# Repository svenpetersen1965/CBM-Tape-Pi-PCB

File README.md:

# CBM-Tape-Pi-PCB
# Preliminary Release of Rev.2
This is the PCB, that I have created for <a href="https://github.com/RhinoDevel/cbmtapepi">RhinoDevel's CBM Tape Pi</a>.

It is <b>not yet tested</b> and this is only a <b>preliminary</b> release!

The PCB has an option for a barrel connector Power Supply. Also, for possible future software development, a rotary encode and an I²C OLED-Display can be connected. This is not yet supported.

Debugging result so far:

There is a screw up with signals <b>BCM11</b>, it shoudl be connected to the collector of Q4, but the signal name is screwed up. A botch wire is required between the collector of Q4/R8 and Pin 23/BCM11 of the Raspberry Pi.

# Rev. 3
Rev. 3 fixes the bug of rev. 2. Also the dimensions have changed: the RasPi was moved 4mm away from the edge connector.

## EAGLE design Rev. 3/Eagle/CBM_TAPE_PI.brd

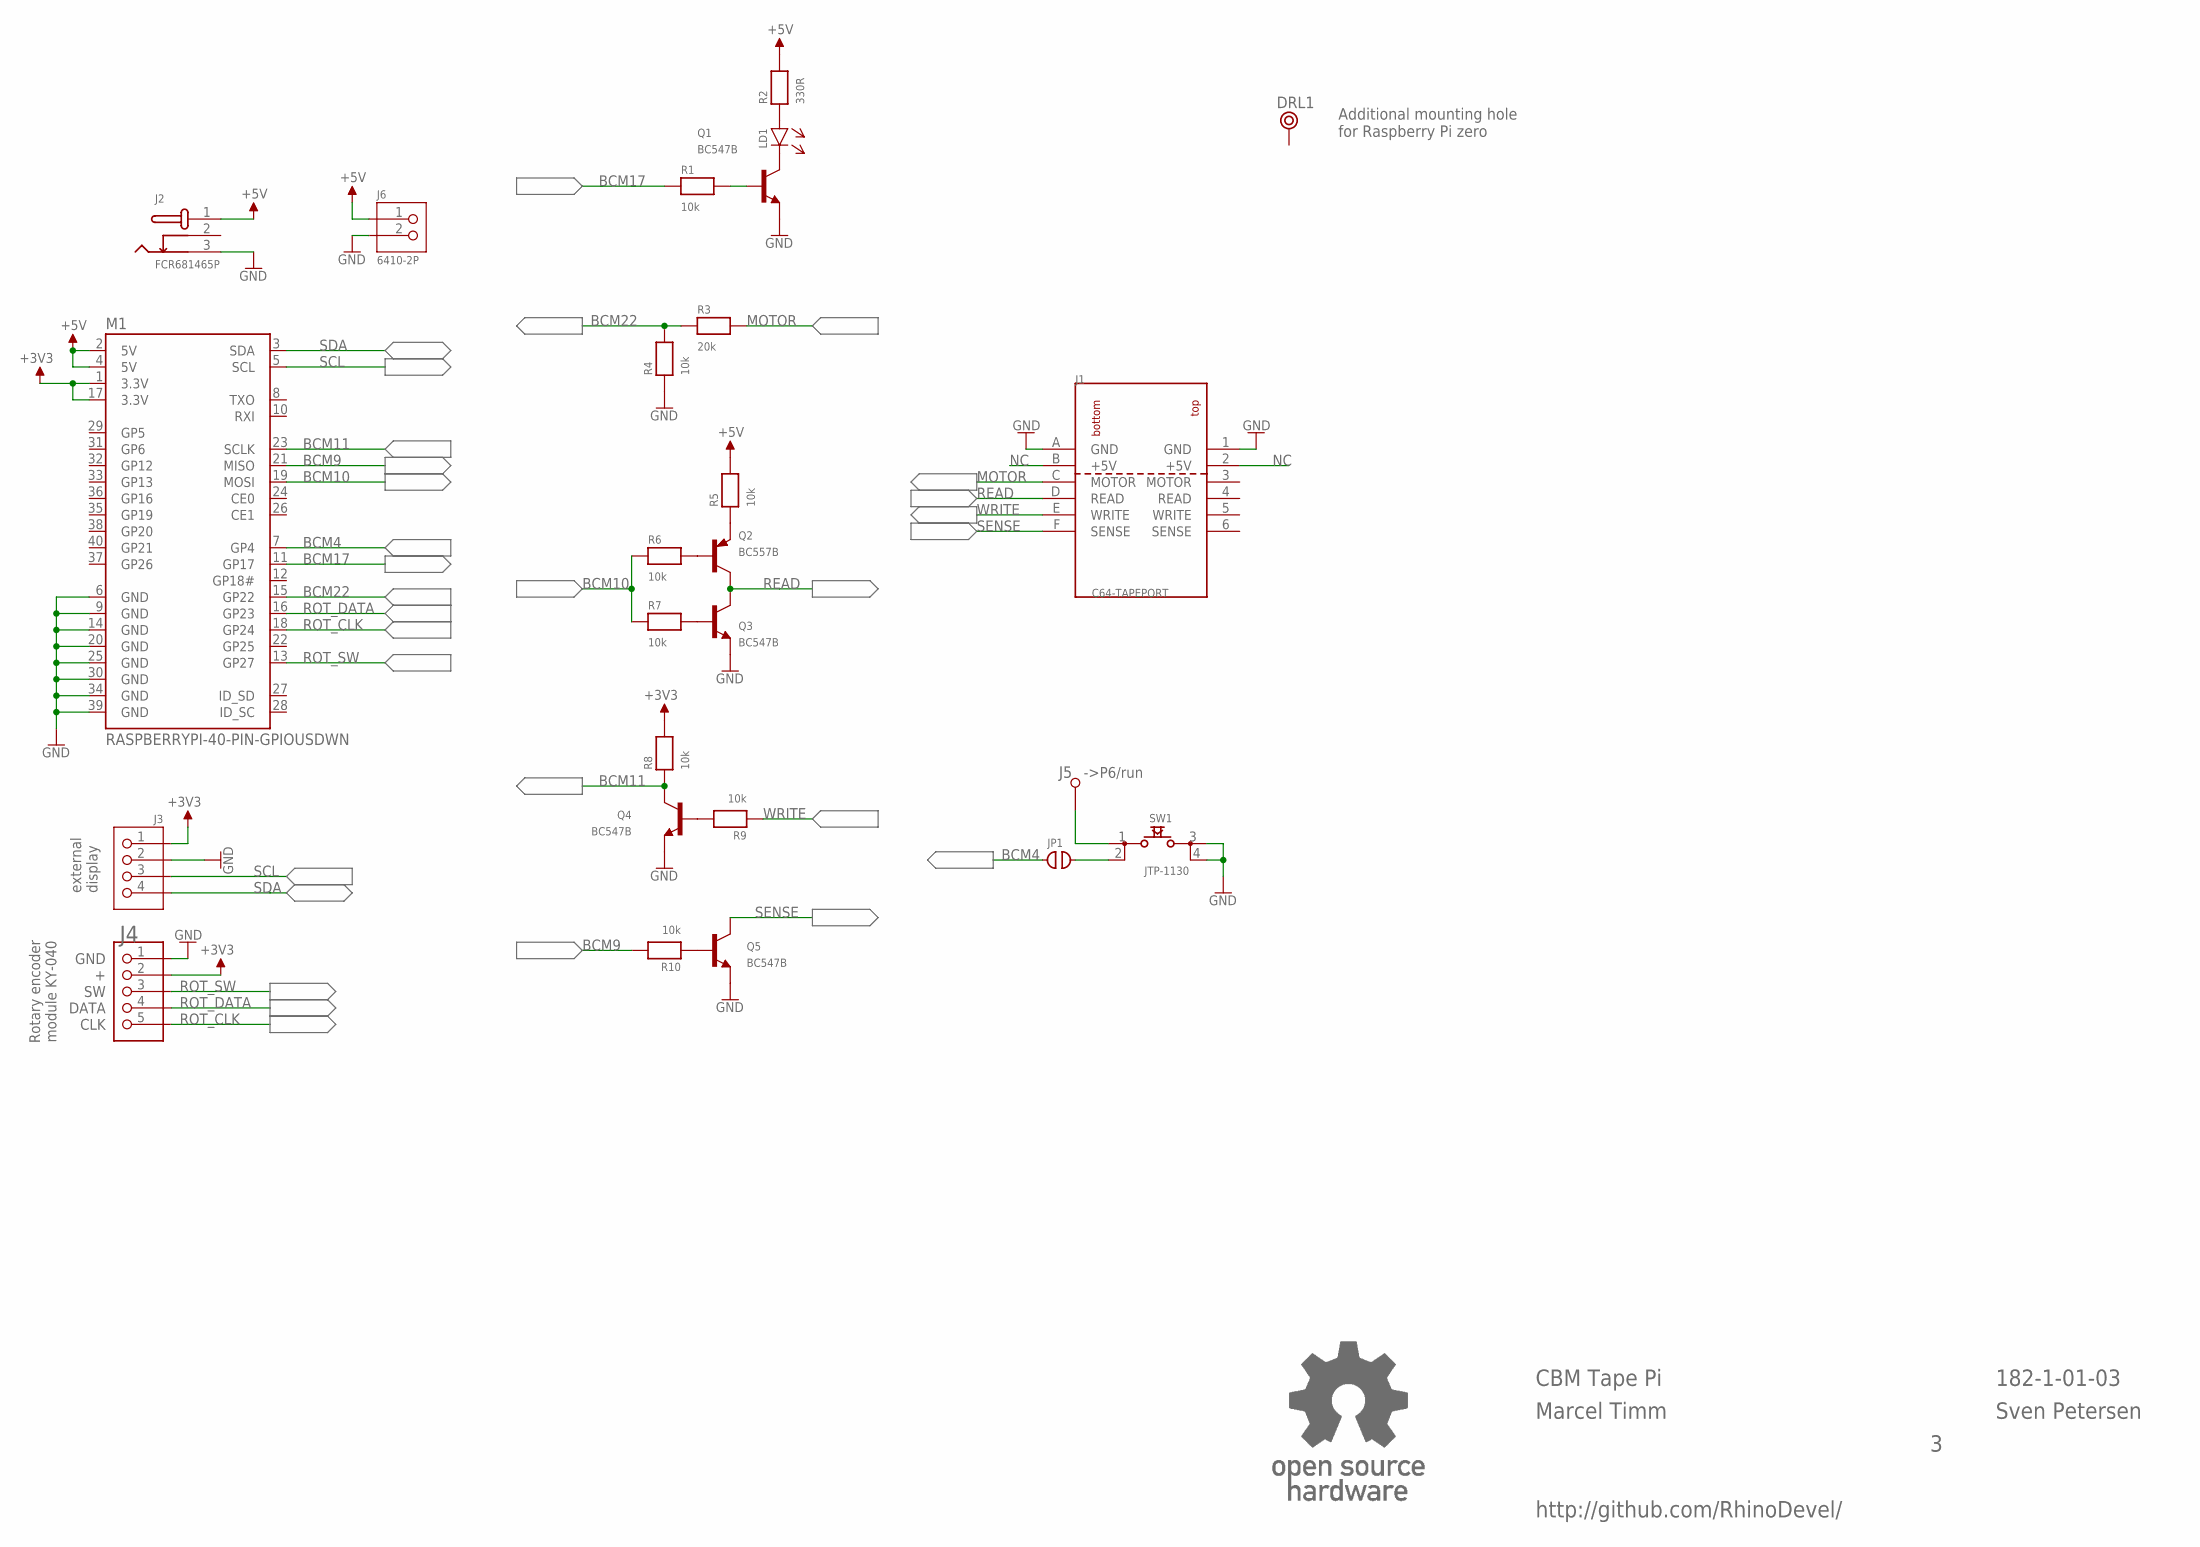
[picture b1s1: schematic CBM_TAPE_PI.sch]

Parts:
DRL1: RPI_MNT; RASPI_MNT
J1: C64-TAPEPORT; TAPEPORT
J2: FCR681465P
J3: 6410-4P
J4: 6410-5P
J5: L1,2_R; 1,2MM_R
J6: 6410-2P
JP1: OPEN; CP_OP
LD1: 3MM
M1: RASPBERRYPI-40-PIN-GPIOUSDWN; PI_HAT_40P_UPSIDEDOWN
Q1, Q3, Q4, Q5: BC547B; TO92
Q2: BC557B; TO92-EBC
R1, R4, R5, R6, R7, R8, R9, R10: 10k; R-10
R2: 330R; R-10
R3: 20k; R-10
SW1: JTP-1130
U$2: OPEN_SOURCE_HW; OPENHW

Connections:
+3V3: J3.1, J4.2, M1.1 (3.3V), M1.17 (3.3V), R8.2
+5V: J2.1, J6.1, M1.2 (5V), M1.4 (5V), R2.2, R5.2
BCM4: JP1.1, M1.7 (GP4)
BCM9: M1.21 (MISO), R10.2
BCM10: M1.19 (MOSI), R6.1, R7.1
BCM11: M1.23 (SCLK), Q4.3 (C), R8.1
BCM17: M1.11 (GP17), R1.1
BCM22: M1.15 (GP22), R3.1, R4.2
GND: J1.1 (GND), J1.A (GND), J2.3, J3.2, J4.1, J6.2, M1.6 (GND), M1.9 (GND), M1.14 (GND), M1.20 (GND), M1.25 (GND), M1.30 (GND), M1.34 (GND), M1.39 (GND), Q1.1 (E), Q3.1 (E), Q4.1 (E), Q5.1 (E), R4.1, SW1.3, SW1.4
MOTOR: J1.C (MOTOR), R3.2
unnamed: Q1.2 (B), R1.2
unnamed: LD1.C (K), Q1.3 (C)
unnamed: LD1.A, R2.1
unnamed: Q2.E, R5.1
unnamed: Q2.B, R6.2
unnamed: Q3.2 (B), R7.2
unnamed: Q4.2 (B), R9.2
unnamed: Q5.2 (B), R10.1
unnamed: J5.1, SW1.1
unnamed: JP1.2, SW1.2
NC: J1.2 (+5V), J1.B (+5V)
READ: J1.D (READ), Q2.C, Q3.3 (C)
ROT_CLK: J4.5, M1.18 (GP24)
ROT_DATA: J4.4, M1.16 (GP23)
ROT_SW: J4.3, M1.13 (GP27)
SCL: J3.3, M1.5 (SCL)
SDA: J3.4, M1.3 (SDA)
SENSE: J1.F (SENSE), Q5.3 (C)
WRITE: J1.E (WRITE), R9.1

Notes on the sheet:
http://github.com/RhinoDevel/
CBM Tape Pi
Sven Petersen
external display
GND
DATA
CLK
Rotary encoder module KY-040
->P6/run
Marcel Timm
182-1-01-03
Additional mounting hole for Raspberry Pi zero

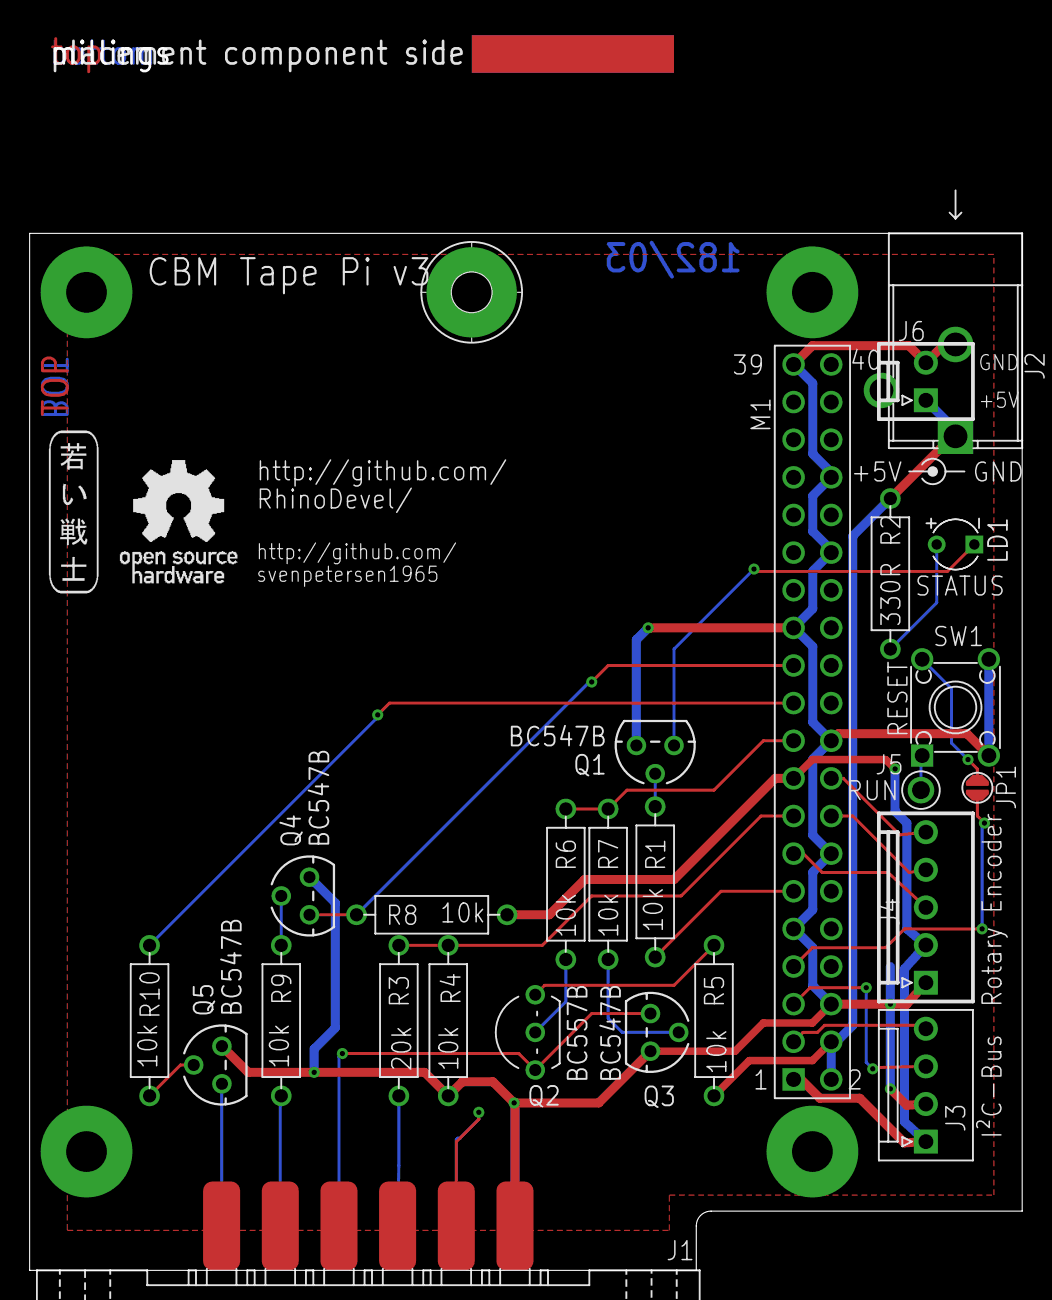
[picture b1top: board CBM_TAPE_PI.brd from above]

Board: 2 copper layers, 67.0 x 83.8 mm, 30 parts (0 on the bottom side), 29 nets.

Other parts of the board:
U$53: 2LAYER
U$54: SVEN_TAG
U$55: PCB-TITLE/

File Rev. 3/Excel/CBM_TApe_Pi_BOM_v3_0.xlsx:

RhinoDevel: CBM Tape Pi Rev. 3
Bill of Material Rev. 3.0
Pos. | Qty | Value | Footprint | Ref.-No. | Comment
1 | 1 | 182-2-01-03 | 2 Layer | PCB Rev. 3 | 2 layer, Cu 35µ, HASL, 70.0mm x 67.0mm, 1.6mm FR4
2 | 1 | 3mm/green | 3MM | LD1 | standard 3mm LED
3 | 1 | KF2510/4p header | 6410-4P | J3 | option: KF2510 or MOLEX 6410/22-27-2041
4 | 1 | KF2510/5p header | 6410-5P | J4 | option: KF2510 or MOLEX 6410/22-27-2051
5 | 8 | 10k | R-10 | R1, R4, R5, R6, R7, R8, R9, R10 | metal film resistor, 10% or better
6 | 1 | 20k | R-10 | R3 | metal film resistor, 10% or better
7 | 1 | 330R | R-10 | R2 | metal film resistor, 10% or better
8 | 1 | KF2510/2p header | 6410-2P | J6 | option: KF2510 or MOLEX 6410/22-27-2021
9 | 4 | BC547B | TO92 | Q1, Q3, Q4, Q5 | NPN Transistor
10 | 1 | BC557B | TO92-EBC | Q2 | PNP Transistror
11 | 1 | 2x6, pitch 3.96mm | TAPEPORT | J1 | edge connector (e.g. 805 type), C64 cassette port
12 | 1 | FCR681465P | FCR681465P | J2 | Cliff, Reichelt: CLIFF FCR681465P, tme.eu: FCR681465P
13 | 1 | JTP-1130 | JTP-1130 | SW1 | 6mm x 6mm tact switch, e.g. Namae Electronics, e.g. Reichelt TASTER 9303
14 | 1 | 1 pin header | 1,2MM_R | J5 | 1 pin header (for dupont wire)
15 | 1 | RASPBERRYPI | PI_HAT_40P_UPSIDEDOWN | M1 | Raspberry Pi zero or other
16 | 1 | MPE 094-2-040 |  | (M1) | MPE, e.g. Reichelt MPE 094-2-040

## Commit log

2021-08-31 Preliminary Release
    This is released untested!
2021-08-31 Create LICENSE
2021-09-13 BCM11 botch wire
